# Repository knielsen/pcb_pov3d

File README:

PCB for 3D POV based on STM32F405 MCU and TLC5955 LED driver.

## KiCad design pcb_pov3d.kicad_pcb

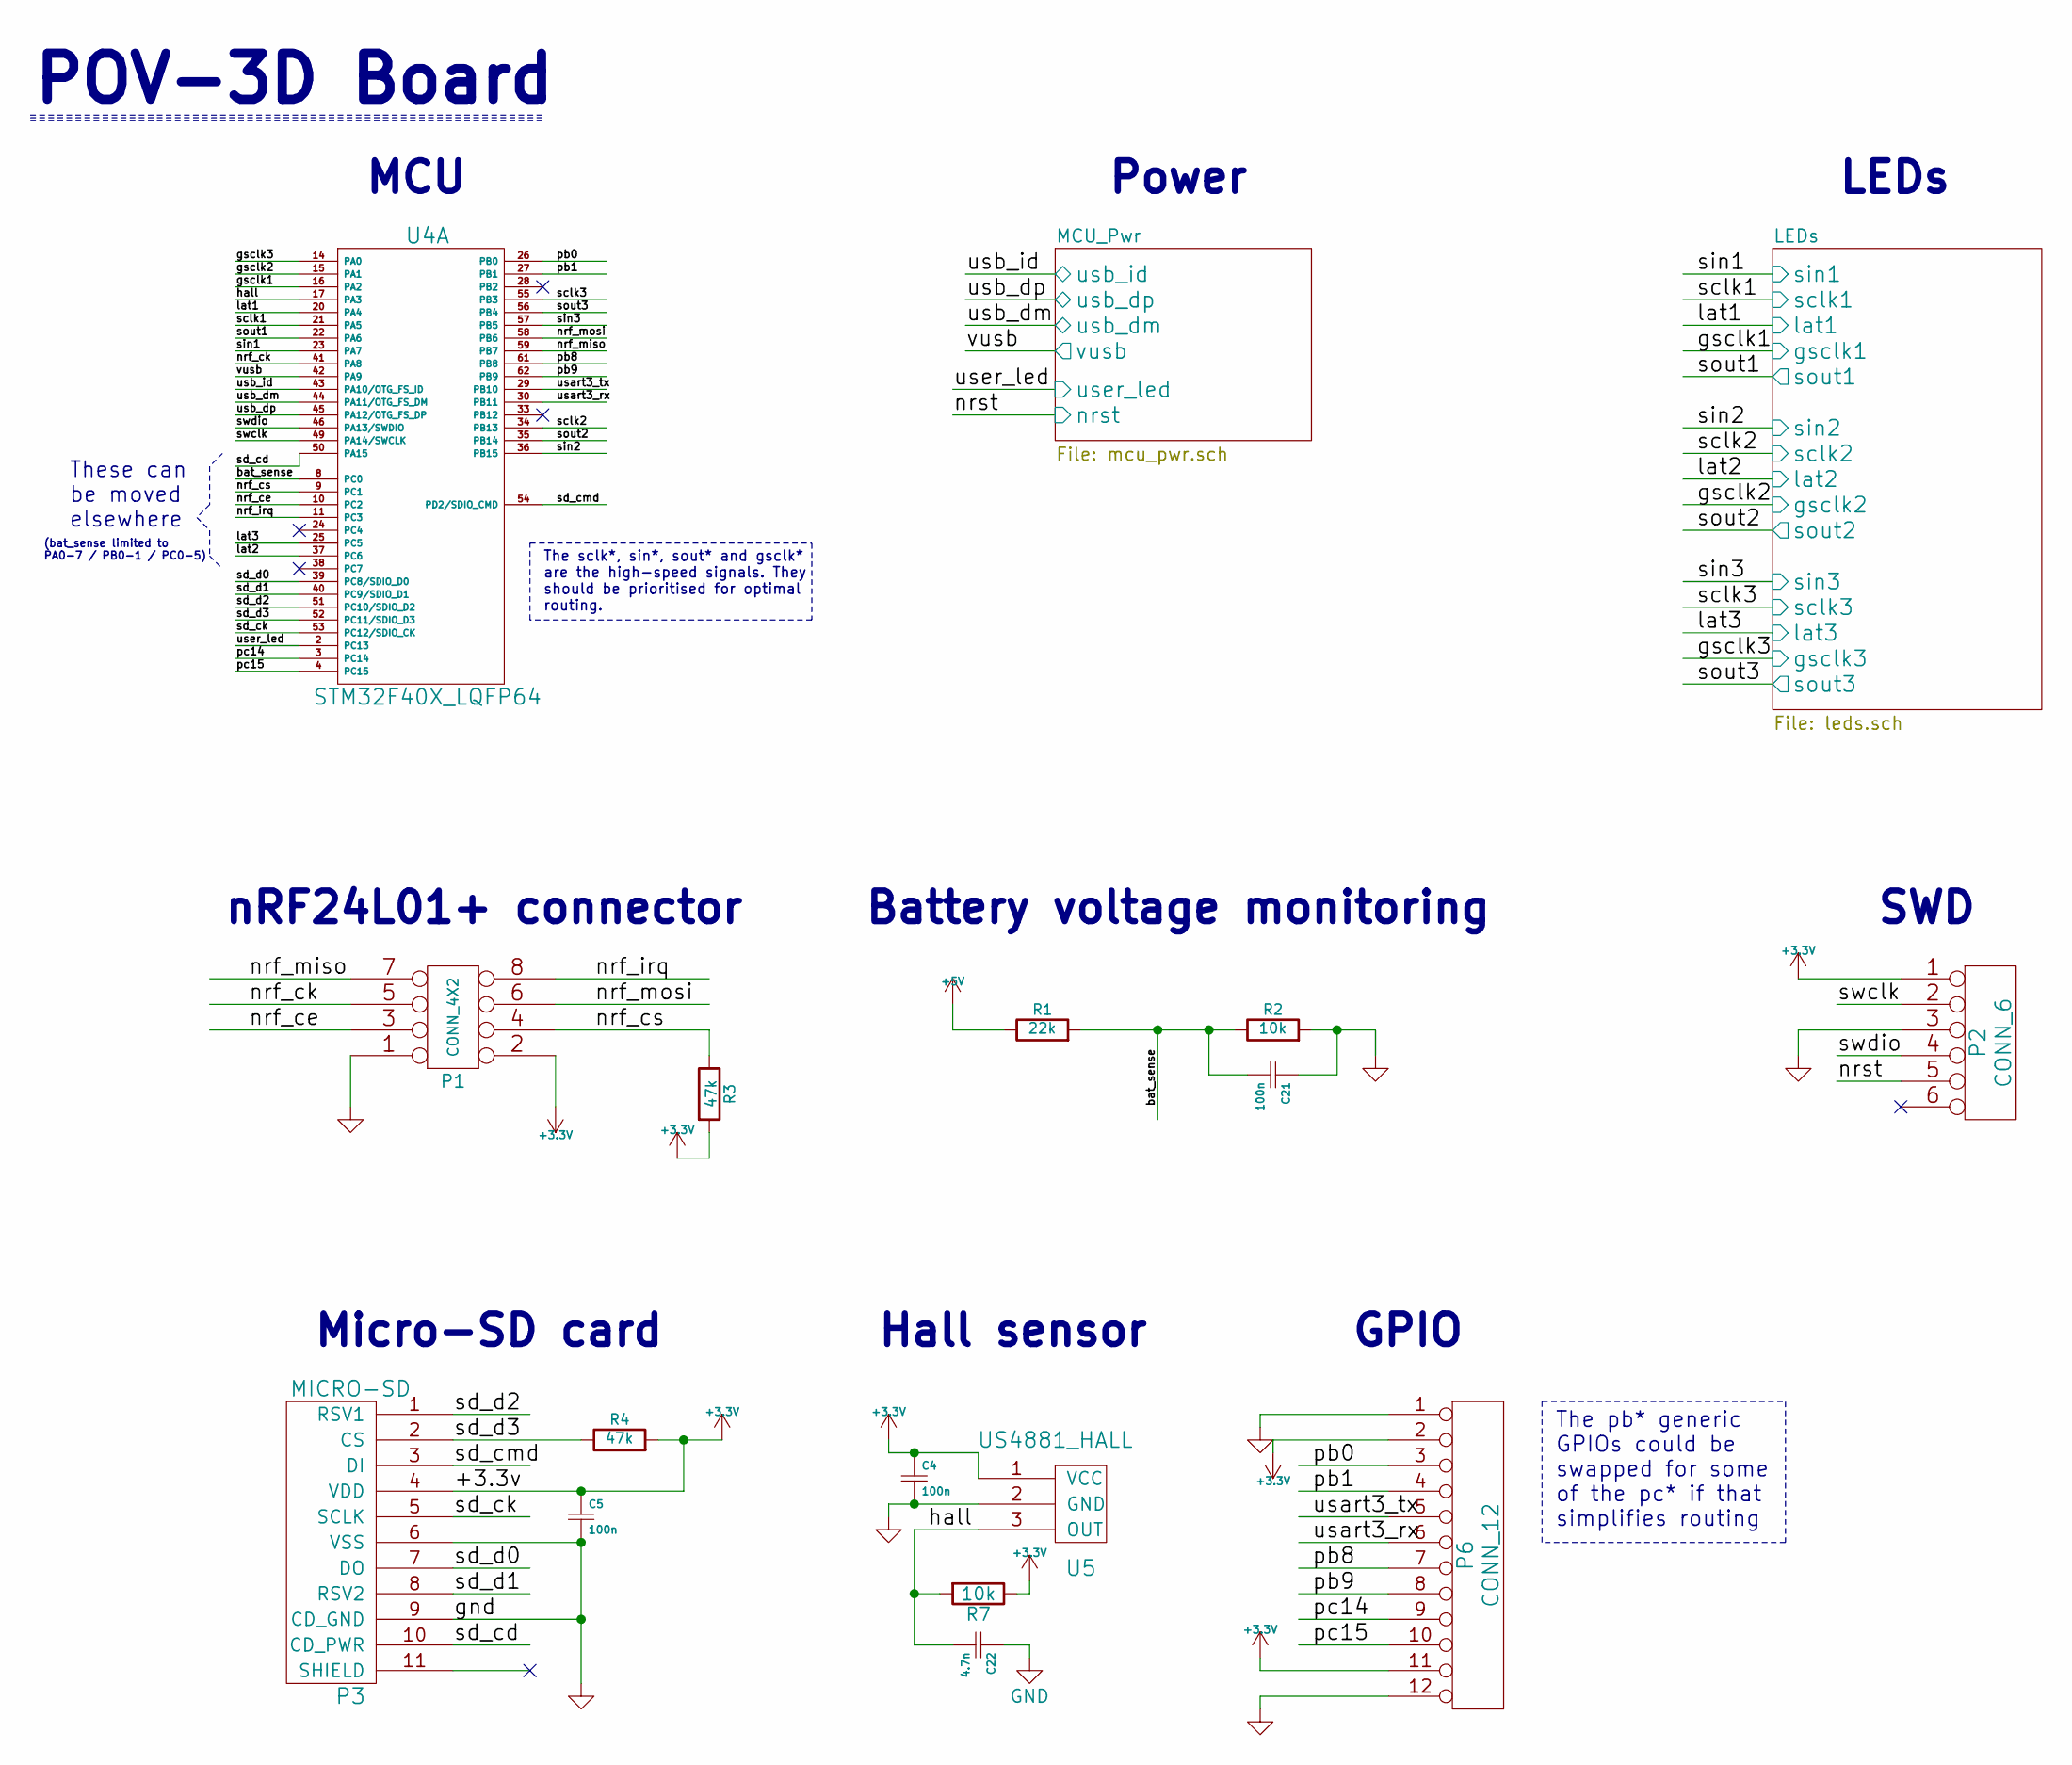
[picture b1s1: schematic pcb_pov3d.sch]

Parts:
C4, C5, C21: 100n; c_0805
C22: 4.7n; c_0805
P1: CONN_4X2; pin_socket_4x2
P2: CONN_6; pin_strip_6
P3: MICRO-SD; SD_502774
P6: CONN_12; pin_strip_12-90
R1: 22k; r_0805
R2, R7: 10k; r_0805
R3, R4: 47k; r_0805
U4: STM32F40X_LQFP64; LQFP_64
U5: US4881_HALL; TO92

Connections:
+3V3: C4.1, C5.1, P1.2, P2.1, P3.4 (VDD), P6.2, P6.11, R3.2, R4.2, R7.1, U5.1 (VCC); also elsewhere on the board
+5V: R1.1; also elsewhere on the board
/LEDs/gsclk1: U4.16 (PA2); also elsewhere on the board
/LEDs/gsclk2: U4.15 (PA1); also elsewhere on the board
/LEDs/gsclk3: U4.14 (PA0); also elsewhere on the board
/LEDs/lat1: U4.20 (PA4); also elsewhere on the board
/LEDs/lat2: U4.37 (PC6); also elsewhere on the board
/LEDs/lat3: U4.25 (PC5); also elsewhere on the board
/LEDs/sclk1: U4.21 (PA5); also elsewhere on the board
/LEDs/sclk2: U4.34 (PB13); also elsewhere on the board
/LEDs/sclk3: U4.55 (PB3); also elsewhere on the board
/LEDs/sin1: U4.23 (PA7); also elsewhere on the board
/LEDs/sin2: U4.36 (PB15); also elsewhere on the board
/LEDs/sin3: U4.57 (PB5); also elsewhere on the board
/LEDs/sout1: U4.22 (PA6); also elsewhere on the board
/LEDs/sout2: U4.35 (PB14); also elsewhere on the board
/LEDs/sout3: U4.56 (PB4); also elsewhere on the board
/MCU_Pwr/nrst: P2.5; also elsewhere on the board
/MCU_Pwr/usb_dm: U4.44 (PA11/OTG_FS_DM); also elsewhere on the board
/MCU_Pwr/usb_dp: U4.45 (PA12/OTG_FS_DP); also elsewhere on the board
/MCU_Pwr/usb_id: U4.43 (PA10/OTG_FS_ID); also elsewhere on the board
/MCU_Pwr/user_led: U4.2 (PC13); also elsewhere on the board
/MCU_Pwr/vusb: U4.42 (PA9); also elsewhere on the board
/bat_sense: C21.2, R1.2, R2.1, U4.8 (PC0)
/hall: C22.2, R7.2, U4.17 (PA3), U5.3 (OUT)
/nrf_ce: P1.3, U4.10 (PC2)
/nrf_ck: P1.5, U4.41 (PA8)
/nrf_cs: P1.4, R3.1, U4.9 (PC1)
/nrf_irq: P1.8, U4.11 (PC3)
/nrf_miso: P1.7, U4.59 (PB7)
/nrf_mosi: P1.6, U4.58 (PB6)
/pb0: P6.3, U4.26 (PB0)
/pb1: P6.4, U4.27 (PB1)
/pb8: P6.7, U4.61 (PB8)
/pb9: P6.8, U4.62 (PB9)
/pc14: P6.9, U4.3 (PC14)
/pc15: P6.10, U4.4 (PC15)
/sd_cd: P3.10 (CD_PWR), U4.50 (PA15)
/sd_ck: P3.5 (SCLK), U4.53 (PC12/SDIO_CK)
/sd_cmd: P3.3 (DI), U4.54 (PD2/SDIO_CMD)
/sd_d0: P3.7 (DO), U4.39 (PC8/SDIO_D0)
/sd_d1: P3.8 (RSV2), U4.40 (PC9/SDIO_D1)
/sd_d2: P3.1 (RSV1), U4.51 (PC10/SDIO_D2)
/sd_d3: P3.2 (CS), R4.1, U4.52 (PC11/SDIO_D3)
/swclk: P2.2, U4.49 (PA14/SWCLK)
/swdio: P2.4, U4.46 (PA13/SWDIO)
/usart3_rx: P6.6, U4.30 (PB11)
/usart3_tx: P6.5, U4.29 (PB10)
GND: C4.2, C5.2, C21.1, C22.1, P1.1, P2.3, P3.6 (VSS), P3.9 (CD_GND), P6.1, P6.12, R2.2, U5.2 (GND); also elsewhere on the board

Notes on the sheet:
nRF24L01+ connector
MCU
Micro-SD card
These can be moved elsewhere
(bat_sense limited to PA0-7 / PB0-1 / PC0-5)
Battery voltage monitoring
Power
LEDs
SWD
Hall sensor
GPIO
POV-3D Board
The sclk*, sin*, sout* and gsclk* are the high-speed signals. They should be prioritised for optimal routing.
The pb* generic GPIOs could be swapped for some of the pc* if that simplifies routing

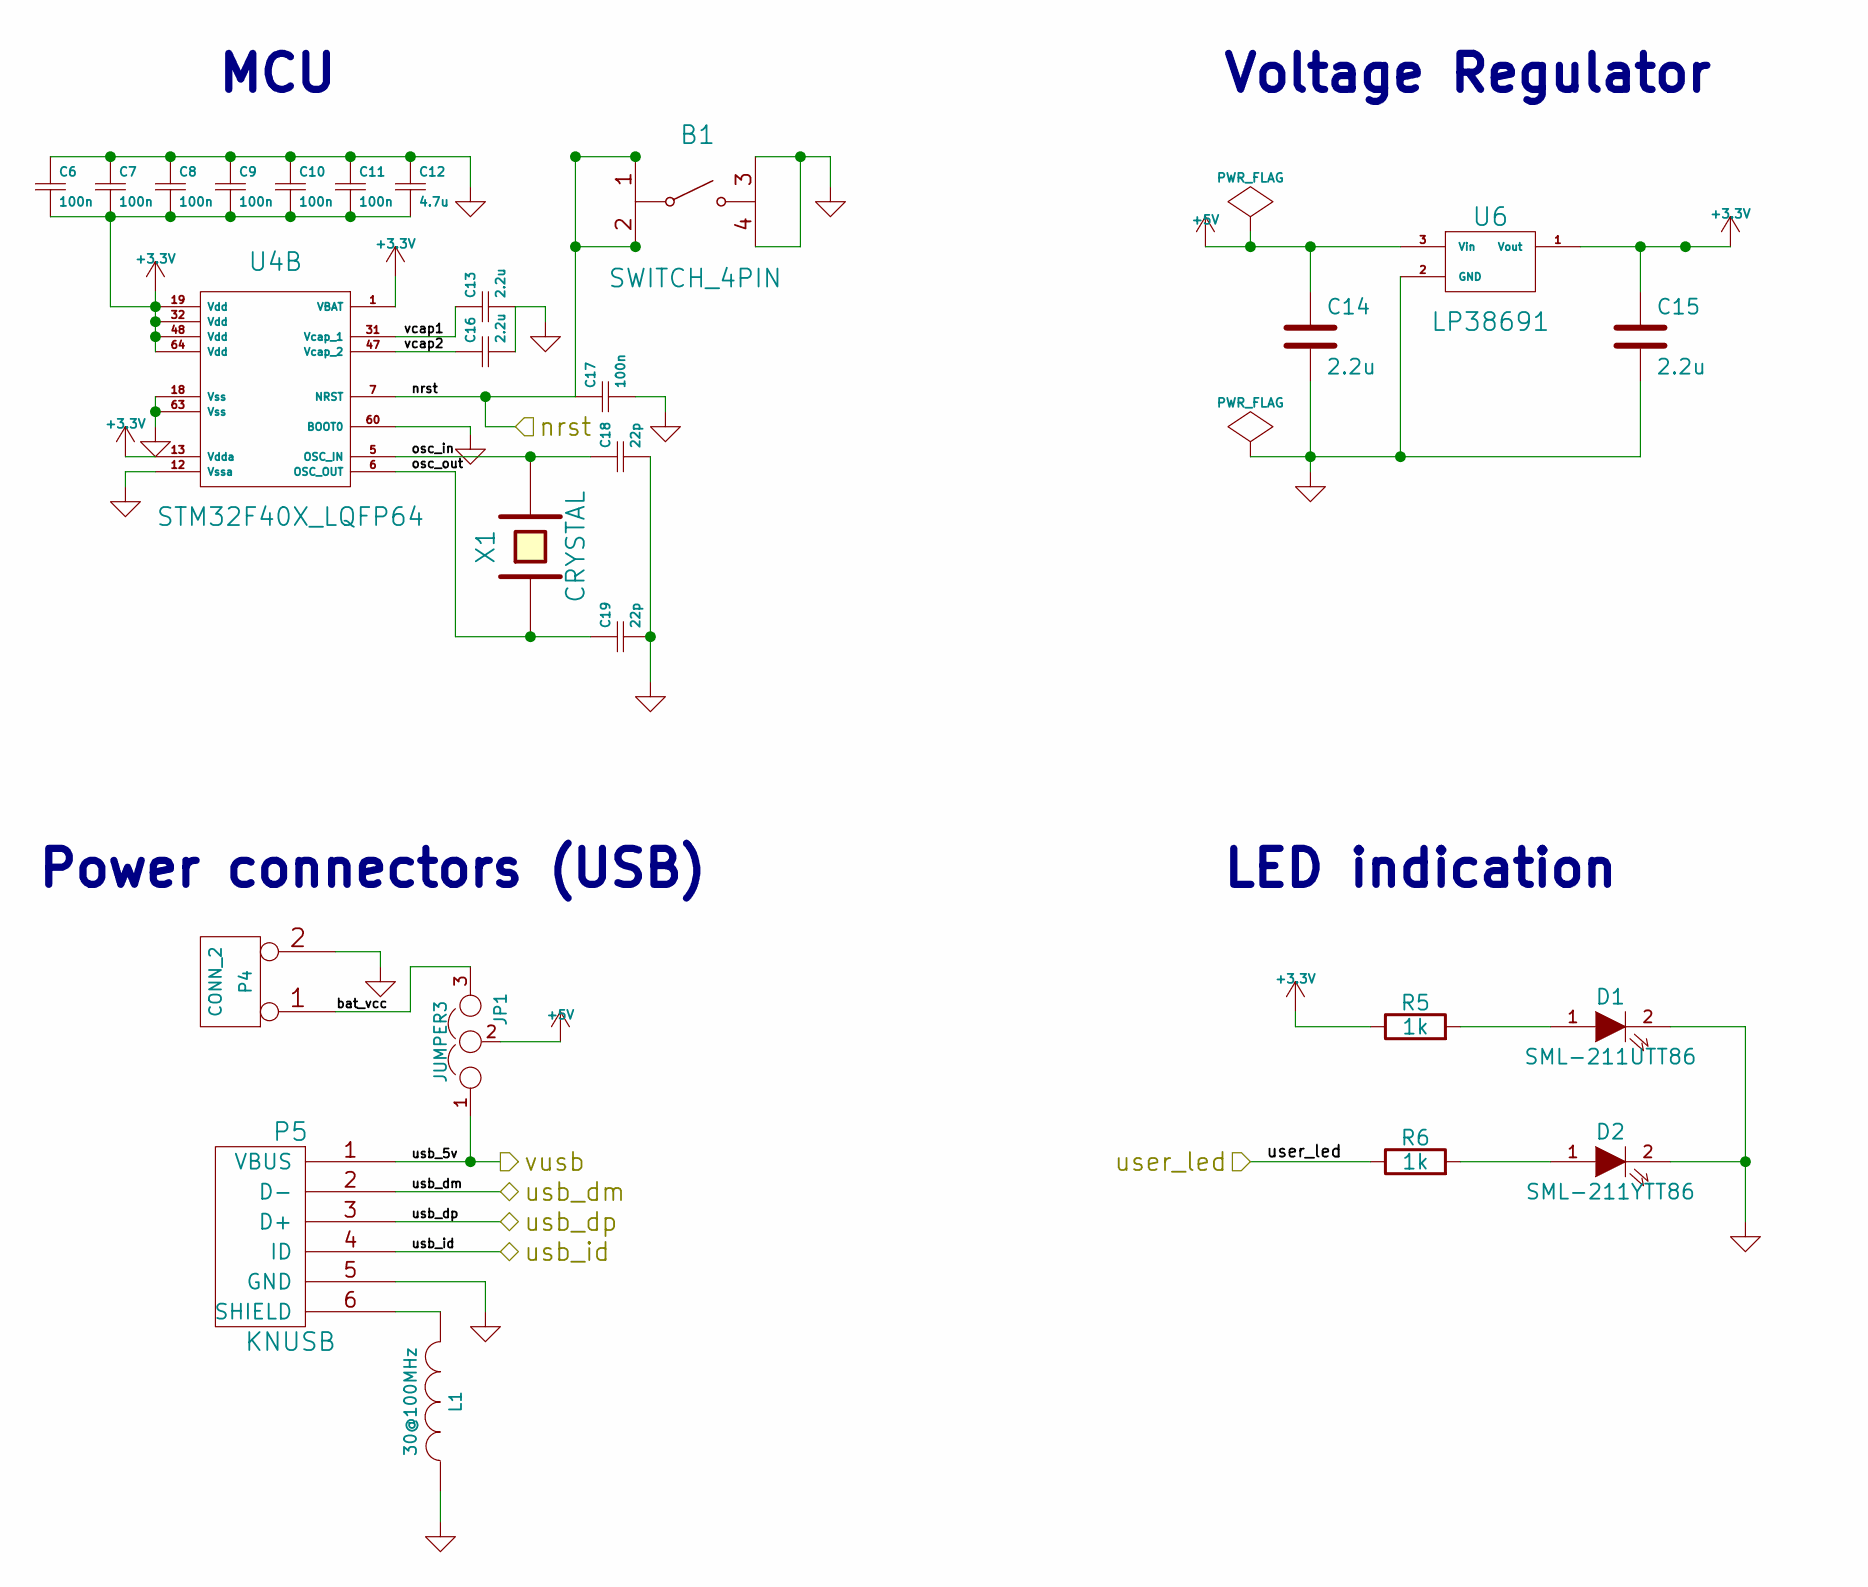
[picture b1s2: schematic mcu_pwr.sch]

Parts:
B1: SWITCH_4PIN; SWITCH_FSMJSMA
C6, C7, C8, C9, C10, C11, C17: 100n; c_0805
C12: 4.7u; c_0805
C13, C14, C15, C16: 2.2u; c_0805
C18, C19: 22p; c_0805
D1: SML-211UTT86; Led_0805
D2: SML-211YTT86; Led_0805
JP1: JUMPER3; pin_strip_3
L1: 30@100MHz; SMD-0603
P4: CONN_2; pin_strip_2-90
P5: KNUSB; 10103594-0001LF
R5, R6: 1k; r_0805
U4: STM32F40X_LQFP64; LQFP_64
U6: LP38691; TO-252-3
X1: CRYSTAL; 2-SOJ

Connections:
+3V3: C6.2, C7.2, C8.2, C9.2, C10.2, C11.2, C12.2, C15.1, R5.1, U4.1 (VBAT), U4.13 (Vdda), U4.19 (Vdd), U4.32 (Vdd), U4.48 (Vdd), U4.64 (Vdd), U6.1 (Vout); also elsewhere on the board
+5V: C14.1, JP1.2, U6.3 (Vin); also elsewhere on the board
/MCU_Pwr/bat_vcc: JP1.3, P4.1
/MCU_Pwr/nrst: B1.1, B1.2, C17.1, U4.7 (NRST); also elsewhere on the board
/MCU_Pwr/osc_in: C18.1, U4.5 (OSC_IN), X1.2
/MCU_Pwr/osc_out: C19.1, U4.6 (OSC_OUT), X1.1
/MCU_Pwr/usb_dm: P5.2 (D-); also elsewhere on the board
/MCU_Pwr/usb_dp: P5.3 (D+); also elsewhere on the board
/MCU_Pwr/usb_id: P5.4 (ID); also elsewhere on the board
/MCU_Pwr/user_led: R6.1; also elsewhere on the board
/MCU_Pwr/vcap1: C13.1, U4.31 (Vcap_1)
/MCU_Pwr/vcap2: C16.1, U4.47 (Vcap_2)
/MCU_Pwr/vusb: JP1.1, P5.1 (VBUS); also elsewhere on the board
GND: B1.3, B1.4, C6.1, C7.1, C8.1, C9.1, C10.1, C11.1, C12.1, C13.2, C14.2, C15.2, C16.2, C17.2, C18.2, C19.2, D1.2 (K), D2.2 (K), L1.1, P4.2 (PM), P5.5 (GND), U4.12 (Vssa), U4.18 (Vss), U4.60 (BOOT0), U4.63 (Vss), U6.2 (GND); also elsewhere on the board
unnamed: D1.1 (A), R5.2
unnamed: D2.1 (A), R6.2
unnamed: L1.2, P5.6 (SHIELD)

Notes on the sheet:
MCU
Voltage Regulator
Power connectors (USB)
LED indication

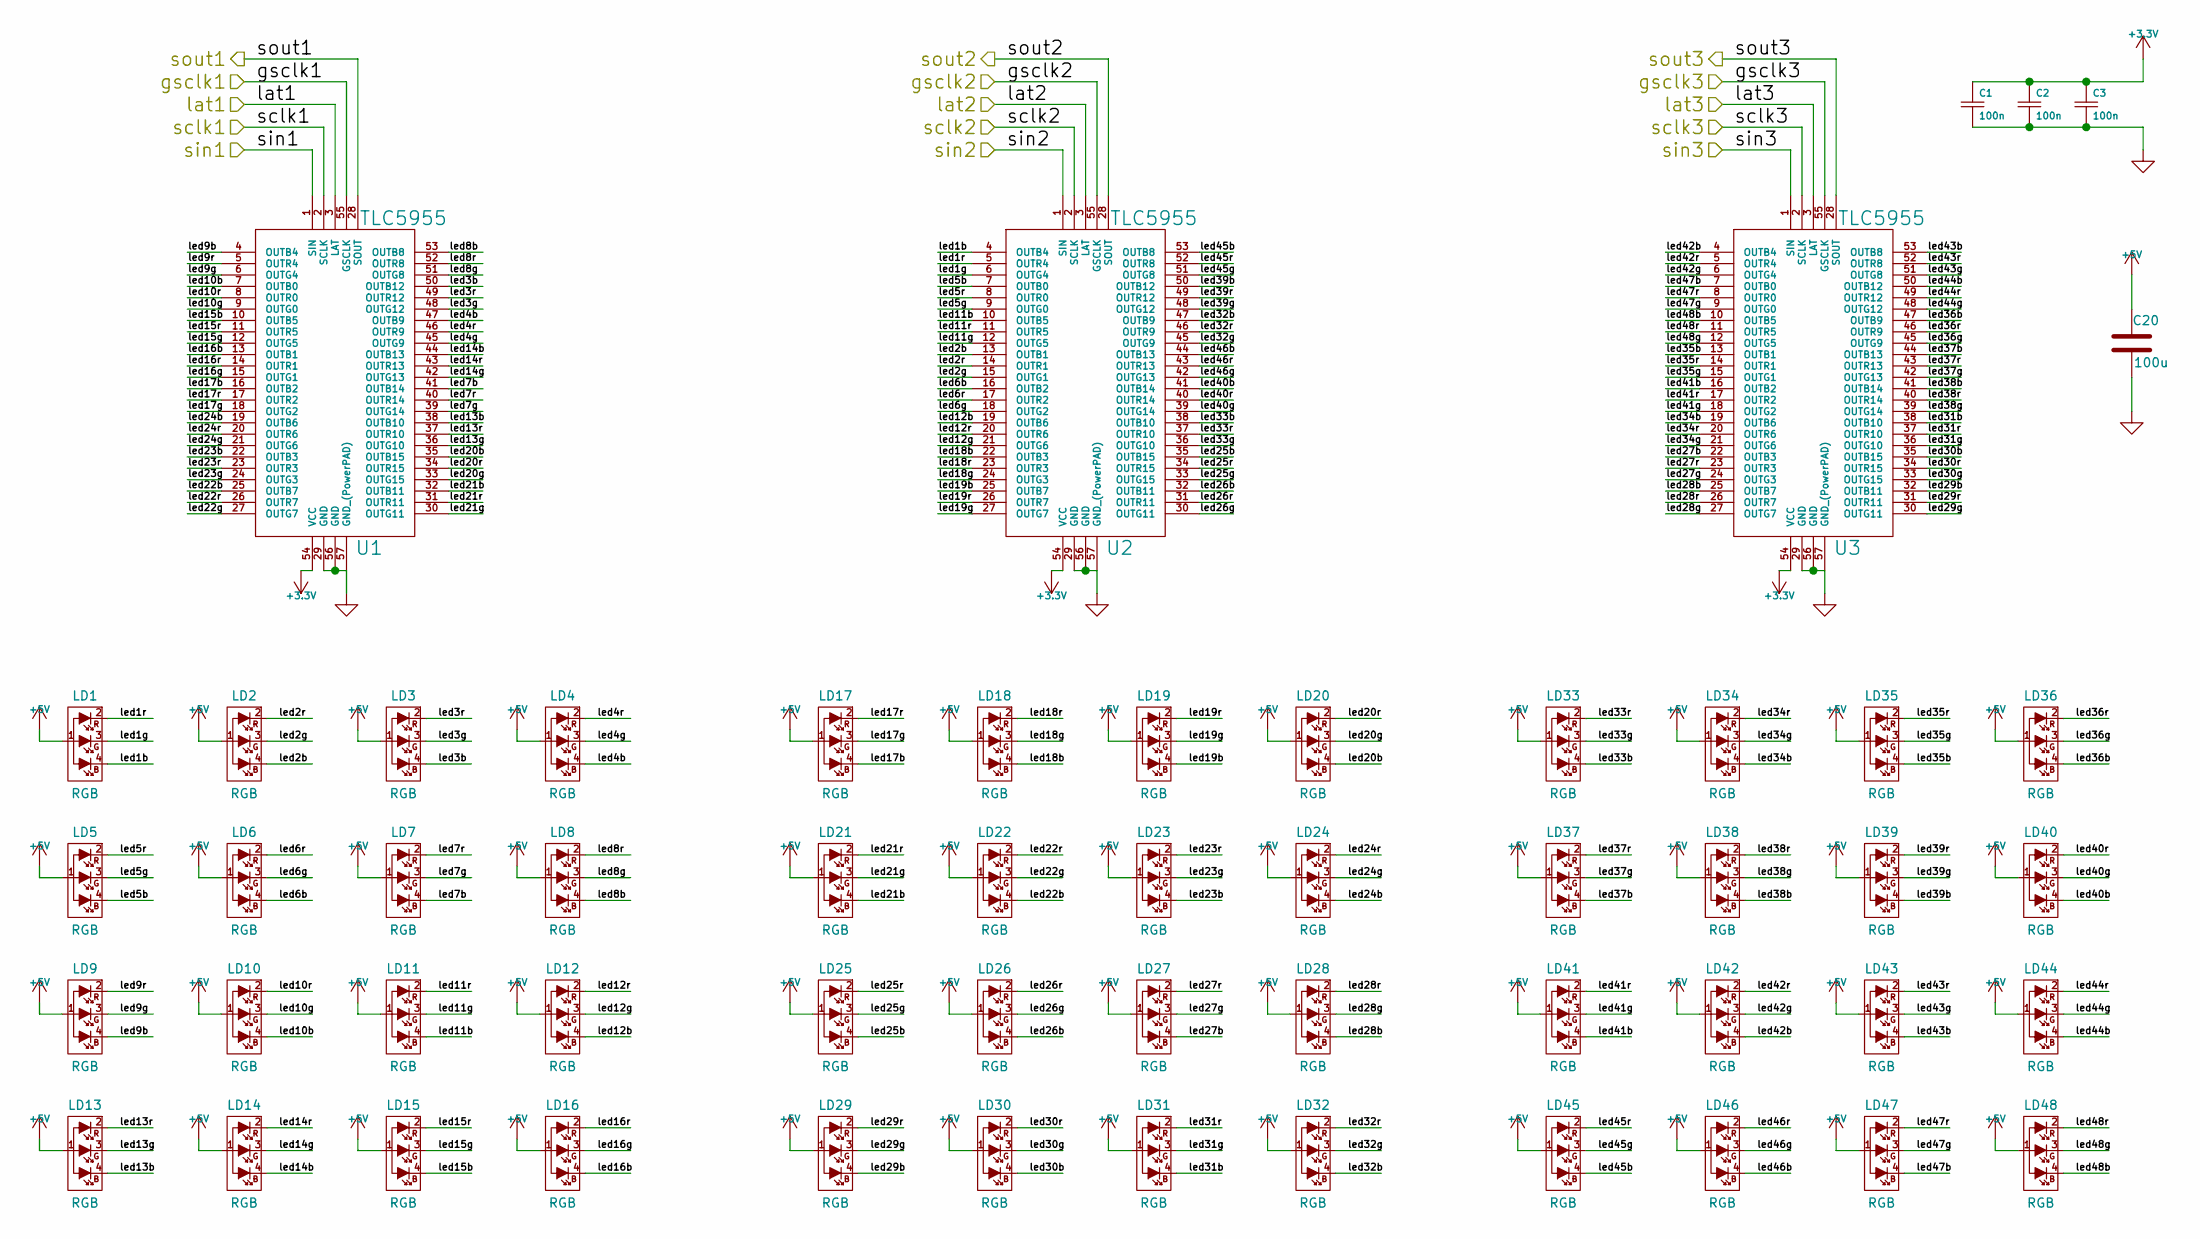
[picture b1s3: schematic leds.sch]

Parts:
C1, C2, C3: 100n; c_0805
C20: 100u; c_elec_6.3x5.8
LD1, LD2, LD3, LD4, LD5, LD6, LD7, LD8, LD9, LD10, LD11, LD12, LD13, LD14, LD15, LD16, LD17, LD18, LD19, LD20, LD21, LD22, LD23, LD24, LD25, LD26, LD27, LD28, LD29, LD30, LD31, LD32, LD33, LD34, LD35, LD36, LD37, LD38, LD39, LD40, LD41, LD42, LD43, LD44, LD45, LD46, LD47, LD48: RGB; RGB_0603
U1, U2, U3: TLC5955; TLC5955DCA

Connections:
+3V3: C1.1, C2.1, C3.1, U1.54 (VCC), U2.54 (VCC), U3.54 (VCC); also elsewhere on the board
+5V: C20.1, LD1.1 (AG), LD2.1 (AG), LD3.1 (AG), LD4.1 (AG), LD5.1 (AG), LD6.1 (AG), LD7.1 (AG), LD8.1 (AG), LD9.1 (AG), LD10.1 (AG), LD11.1 (AG), LD12.1 (AG), LD13.1 (AG), LD14.1 (AG), LD15.1 (AG), LD16.1 (AG), LD17.1 (AG), LD18.1 (AG), LD19.1 (AG), LD20.1 (AG), LD21.1 (AG), LD22.1 (AG), LD23.1 (AG), LD24.1 (AG), LD25.1 (AG), LD26.1 (AG), LD27.1 (AG), LD28.1 (AG), LD29.1 (AG), LD30.1 (AG), LD31.1 (AG), LD32.1 (AG), LD33.1 (AG), LD34.1 (AG), LD35.1 (AG), LD36.1 (AG), LD37.1 (AG), LD38.1 (AG), LD39.1 (AG), LD40.1 (AG), LD41.1 (AG), LD42.1 (AG), LD43.1 (AG), LD44.1 (AG), LD45.1 (AG), LD46.1 (AG), LD47.1 (AG), LD48.1 (AG); also elsewhere on the board
/LEDs/gsclk1: U1.55 (GSCLK); also elsewhere on the board
/LEDs/gsclk2: U2.55 (GSCLK); also elsewhere on the board
/LEDs/gsclk3: U3.55 (GSCLK); also elsewhere on the board
/LEDs/lat1: U1.3 (LAT); also elsewhere on the board
/LEDs/lat2: U2.3 (LAT); also elsewhere on the board
/LEDs/lat3: U3.3 (LAT); also elsewhere on the board
/LEDs/led1b: LD1.4 (CB), U2.4 (OUTB4)
/LEDs/led1g: LD1.3 (CG), U2.6 (OUTG4)
/LEDs/led1r: LD1.2 (CR), U2.5 (OUTR4)
/LEDs/led2b: LD2.4 (CB), U2.13 (OUTB1)
/LEDs/led2g: LD2.3 (CG), U2.15 (OUTG1)
/LEDs/led2r: LD2.2 (CR), U2.14 (OUTR1)
/LEDs/led3b: LD3.4 (CB), U1.50 (OUTB12)
/LEDs/led3g: LD3.3 (CG), U1.48 (OUTG12)
/LEDs/led3r: LD3.2 (CR), U1.49 (OUTR12)
/LEDs/led4b: LD4.4 (CB), U1.47 (OUTB9)
/LEDs/led4g: LD4.3 (CG), U1.45 (OUTG9)
/LEDs/led4r: LD4.2 (CR), U1.46 (OUTR9)
/LEDs/led5b: LD5.4 (CB), U2.7 (OUTB0)
/LEDs/led5g: LD5.3 (CG), U2.9 (OUTG0)
/LEDs/led5r: LD5.2 (CR), U2.8 (OUTR0)
/LEDs/led6b: LD6.4 (CB), U2.16 (OUTB2)
/LEDs/led6g: LD6.3 (CG), U2.18 (OUTG2)
/LEDs/led6r: LD6.2 (CR), U2.17 (OUTR2)
/LEDs/led7b: LD7.4 (CB), U1.41 (OUTB14)
/LEDs/led7g: LD7.3 (CG), U1.39 (OUTG14)
/LEDs/led7r: LD7.2 (CR), U1.40 (OUTR14)
/LEDs/led8b: LD8.4 (CB), U1.53 (OUTB8)
/LEDs/led8g: LD8.3 (CG), U1.51 (OUTG8)
/LEDs/led8r: LD8.2 (CR), U1.52 (OUTR8)
/LEDs/led9b: LD9.4 (CB), U1.4 (OUTB4)
/LEDs/led9g: LD9.3 (CG), U1.6 (OUTG4)
/LEDs/led9r: LD9.2 (CR), U1.5 (OUTR4)
/LEDs/led10b: LD10.4 (CB), U1.7 (OUTB0)
/LEDs/led10g: LD10.3 (CG), U1.9 (OUTG0)
/LEDs/led10r: LD10.2 (CR), U1.8 (OUTR0)
/LEDs/led11b: LD11.4 (CB), U2.10 (OUTB5)
/LEDs/led11g: LD11.3 (CG), U2.12 (OUTG5)
/LEDs/led11r: LD11.2 (CR), U2.11 (OUTR5)
/LEDs/led12b: LD12.4 (CB), U2.19 (OUTB6)
/LEDs/led12g: LD12.3 (CG), U2.21 (OUTG6)
/LEDs/led12r: LD12.2 (CR), U2.20 (OUTR6)
/LEDs/led13b: LD13.4 (CB), U1.38 (OUTB10)
/LEDs/led13g: LD13.3 (CG), U1.36 (OUTG10)
/LEDs/led13r: LD13.2 (CR), U1.37 (OUTR10)
/LEDs/led14b: LD14.4 (CB), U1.44 (OUTB13)
/LEDs/led14g: LD14.3 (CG), U1.42 (OUTG13)
/LEDs/led14r: LD14.2 (CR), U1.43 (OUTR13)
/LEDs/led15b: LD15.4 (CB), U1.10 (OUTB5)
/LEDs/led15g: LD15.3 (CG), U1.12 (OUTG5)
/LEDs/led15r: LD15.2 (CR), U1.11 (OUTR5)
/LEDs/led16b: LD16.4 (CB), U1.13 (OUTB1)
/LEDs/led16g: LD16.3 (CG), U1.15 (OUTG1)
/LEDs/led16r: LD16.2 (CR), U1.14 (OUTR1)
/LEDs/led17b: LD17.4 (CB), U1.16 (OUTB2)
/LEDs/led17g: LD17.3 (CG), U1.18 (OUTG2)
/LEDs/led17r: LD17.2 (CR), U1.17 (OUTR2)
/LEDs/led18b: LD18.4 (CB), U2.22 (OUTB3)
/LEDs/led18g: LD18.3 (CG), U2.24 (OUTG3)
/LEDs/led18r: LD18.2 (CR), U2.23 (OUTR3)
/LEDs/led19b: LD19.4 (CB), U2.25 (OUTB7)
/LEDs/led19g: LD19.3 (CG), U2.27 (OUTG7)
/LEDs/led19r: LD19.2 (CR), U2.26 (OUTR7)
/LEDs/led20b: LD20.4 (CB), U1.35 (OUTB15)
/LEDs/led20g: LD20.3 (CG), U1.33 (OUTG15)
/LEDs/led20r: LD20.2 (CR), U1.34 (OUTR15)
/LEDs/led21b: LD21.4 (CB), U1.32 (OUTB11)
/LEDs/led21g: LD21.3 (CG), U1.30 (OUTG11)
/LEDs/led21r: LD21.2 (CR), U1.31 (OUTR11)
/LEDs/led22b: LD22.4 (CB), U1.25 (OUTB7)
/LEDs/led22g: LD22.3 (CG), U1.27 (OUTG7)
/LEDs/led22r: LD22.2 (CR), U1.26 (OUTR7)
/LEDs/led23b: LD23.4 (CB), U1.22 (OUTB3)
/LEDs/led23g: LD23.3 (CG), U1.24 (OUTG3)
/LEDs/led23r: LD23.2 (CR), U1.23 (OUTR3)
/LEDs/led24b: LD24.4 (CB), U1.19 (OUTB6)
/LEDs/led24g: LD24.3 (CG), U1.21 (OUTG6)
/LEDs/led24r: LD24.2 (CR), U1.20 (OUTR6)
/LEDs/led25b: LD25.4 (CB), U2.35 (OUTB15)
/LEDs/led25g: LD25.3 (CG), U2.33 (OUTG15)
/LEDs/led25r: LD25.2 (CR), U2.34 (OUTR15)
/LEDs/led26b: LD26.4 (CB), U2.32 (OUTB11)
/LEDs/led26g: LD26.3 (CG), U2.30 (OUTG11)
/LEDs/led26r: LD26.2 (CR), U2.31 (OUTR11)
/LEDs/led27b: LD27.4 (CB), U3.22 (OUTB3)
/LEDs/led27g: LD27.3 (CG), U3.24 (OUTG3)
/LEDs/led27r: LD27.2 (CR), U3.23 (OUTR3)
/LEDs/led28b: LD28.4 (CB), U3.25 (OUTB7)
/LEDs/led28g: LD28.3 (CG), U3.27 (OUTG7)
/LEDs/led28r: LD28.2 (CR), U3.26 (OUTR7)
/LEDs/led29b: LD29.4 (CB), U3.32 (OUTB11)
/LEDs/led29g: LD29.3 (CG), U3.30 (OUTG11)
/LEDs/led29r: LD29.2 (CR), U3.31 (OUTR11)
/LEDs/led30b: LD30.4 (CB), U3.35 (OUTB15)
/LEDs/led30g: LD30.3 (CG), U3.33 (OUTG15)
/LEDs/led30r: LD30.2 (CR), U3.34 (OUTR15)
/LEDs/led31b: LD31.4 (CB), U3.38 (OUTB10)
/LEDs/led31g: LD31.3 (CG), U3.36 (OUTG10)
/LEDs/led31r: LD31.2 (CR), U3.37 (OUTR10)
/LEDs/led32b: LD32.4 (CB), U2.47 (OUTB9)
/LEDs/led32g: LD32.3 (CG), U2.45 (OUTG9)
/LEDs/led32r: LD32.2 (CR), U2.46 (OUTR9)
/LEDs/led33b: LD33.4 (CB), U2.38 (OUTB10)
/LEDs/led33g: LD33.3 (CG), U2.36 (OUTG10)
/LEDs/led33r: LD33.2 (CR), U2.37 (OUTR10)
/LEDs/led34b: LD34.4 (CB), U3.19 (OUTB6)
/LEDs/led34g: LD34.3 (CG), U3.21 (OUTG6)
/LEDs/led34r: LD34.2 (CR), U3.20 (OUTR6)
/LEDs/led35b: LD35.4 (CB), U3.13 (OUTB1)
/LEDs/led35g: LD35.3 (CG), U3.15 (OUTG1)
/LEDs/led35r: LD35.2 (CR), U3.14 (OUTR1)
/LEDs/led36b: LD36.4 (CB), U3.47 (OUTB9)
/LEDs/led36g: LD36.3 (CG), U3.45 (OUTG9)
/LEDs/led36r: LD36.2 (CR), U3.46 (OUTR9)
/LEDs/led37b: LD37.4 (CB), U3.44 (OUTB13)
/LEDs/led37g: LD37.3 (CG), U3.42 (OUTG13)
/LEDs/led37r: LD37.2 (CR), U3.43 (OUTR13)
/LEDs/led38b: LD38.4 (CB), U3.41 (OUTB14)
/LEDs/led38g: LD38.3 (CG), U3.39 (OUTG14)
/LEDs/led38r: LD38.2 (CR), U3.40 (OUTR14)
/LEDs/led39b: LD39.4 (CB), U2.50 (OUTB12)
/LEDs/led39g: LD39.3 (CG), U2.48 (OUTG12)
/LEDs/led39r: LD39.2 (CR), U2.49 (OUTR12)
/LEDs/led40b: LD40.4 (CB), U2.41 (OUTB14)
/LEDs/led40g: LD40.3 (CG), U2.39 (OUTG14)
/LEDs/led40r: LD40.2 (CR), U2.40 (OUTR14)
/LEDs/led41b: LD41.4 (CB), U3.16 (OUTB2)
/LEDs/led41g: LD41.3 (CG), U3.18 (OUTG2)
/LEDs/led41r: LD41.2 (CR), U3.17 (OUTR2)
/LEDs/led42b: LD42.4 (CB), U3.4 (OUTB4)
/LEDs/led42g: LD42.3 (CG), U3.6 (OUTG4)
/LEDs/led42r: LD42.2 (CR), U3.5 (OUTR4)
/LEDs/led43b: LD43.4 (CB), U3.53 (OUTB8)
/LEDs/led43g: LD43.3 (CG), U3.51 (OUTG8)
/LEDs/led43r: LD43.2 (CR), U3.52 (OUTR8)
/LEDs/led44b: LD44.4 (CB), U3.50 (OUTB12)
/LEDs/led44g: LD44.3 (CG), U3.48 (OUTG12)
/LEDs/led44r: LD44.2 (CR), U3.49 (OUTR12)
/LEDs/led45b: LD45.4 (CB), U2.53 (OUTB8)
/LEDs/led45g: LD45.3 (CG), U2.51 (OUTG8)
/LEDs/led45r: LD45.2 (CR), U2.52 (OUTR8)
/LEDs/led46b: LD46.4 (CB), U2.44 (OUTB13)
/LEDs/led46g: LD46.3 (CG), U2.42 (OUTG13)
/LEDs/led46r: LD46.2 (CR), U2.43 (OUTR13)
/LEDs/led47b: LD47.4 (CB), U3.7 (OUTB0)
/LEDs/led47g: LD47.3 (CG), U3.9 (OUTG0)
/LEDs/led47r: LD47.2 (CR), U3.8 (OUTR0)
/LEDs/led48b: LD48.4 (CB), U3.10 (OUTB5)
/LEDs/led48g: LD48.3 (CG), U3.12 (OUTG5)
/LEDs/led48r: LD48.2 (CR), U3.11 (OUTR5)
/LEDs/sclk1: U1.2 (SCLK); also elsewhere on the board
/LEDs/sclk2: U2.2 (SCLK); also elsewhere on the board
/LEDs/sclk3: U3.2 (SCLK); also elsewhere on the board
/LEDs/sin1: U1.1 (SIN); also elsewhere on the board
/LEDs/sin2: U2.1 (SIN); also elsewhere on the board
/LEDs/sin3: U3.1 (SIN); also elsewhere on the board
/LEDs/sout1: U1.28 (SOUT); also elsewhere on the board
/LEDs/sout2: U2.28 (SOUT); also elsewhere on the board
/LEDs/sout3: U3.28 (SOUT); also elsewhere on the board
GND: C1.2, C2.2, C3.2, C20.2, U1.29 (GND), U1.56 (GND), U1.57 (GND_(PowerPAD)), U2.29 (GND), U2.56 (GND), U2.57 (GND_(PowerPAD)), U3.29 (GND), U3.56 (GND), U3.57 (GND_(PowerPAD)); also elsewhere on the board

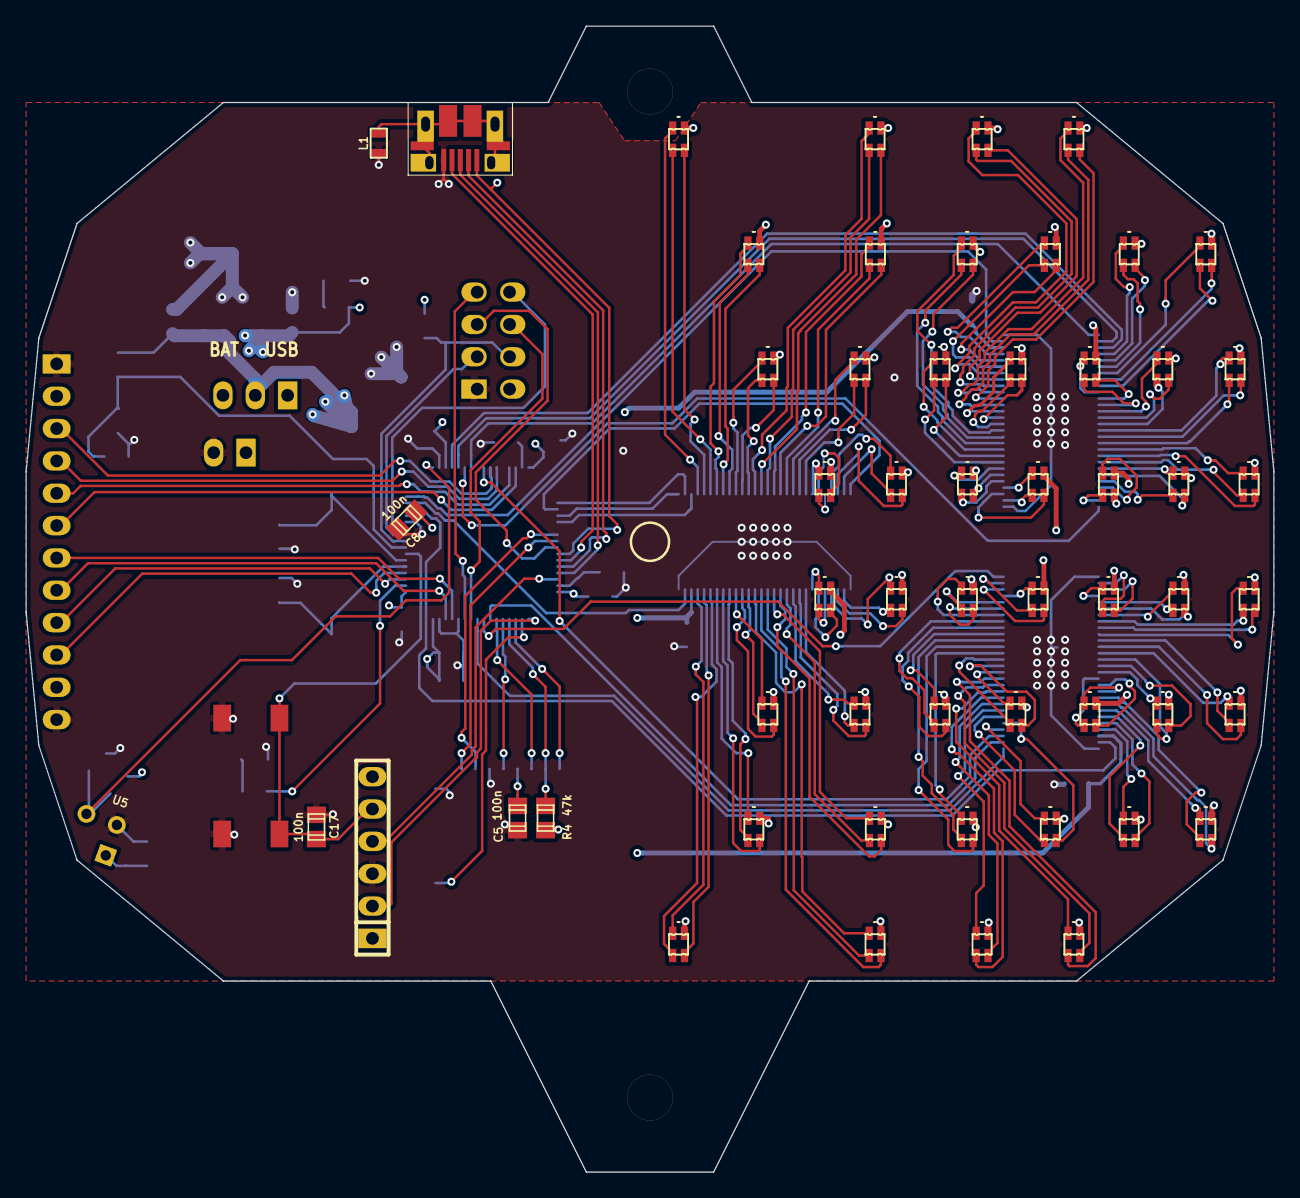
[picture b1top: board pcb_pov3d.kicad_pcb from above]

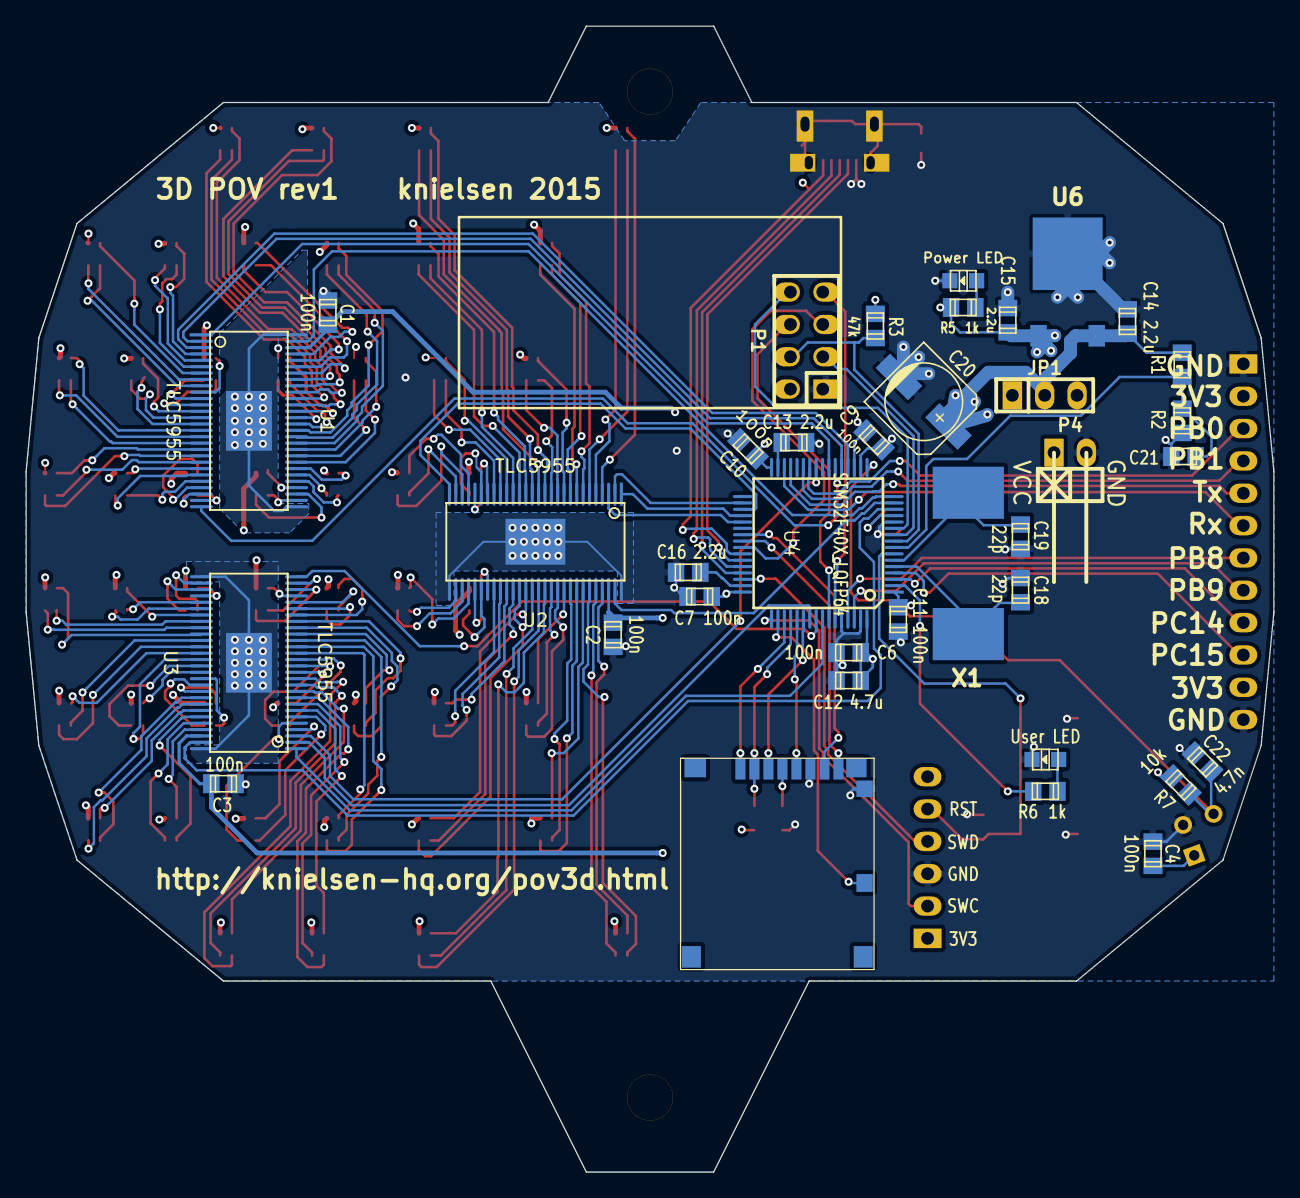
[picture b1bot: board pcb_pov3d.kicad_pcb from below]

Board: 4 copper layers, 98.0 x 90.0 mm, 95 parts (37 on the bottom side), 201 nets.

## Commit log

2015-01-10 Add tlc5955 powerpad to schematics
2015-01-11 Misc. tweaks. Schematics is getting closer now.
2015-01-18 Tweaks.
2015-01-28 Updated for new KiCAD version (though still a few glitches in the schematics)
2015-01-28 Fix CSMALL <-> Csmall glitch when converting to new version
2015-01-28 Fix offset on multi-line texts after import to new KiCAD version.
2015-01-28 Place RGB LEDs in the computed pattern for 3D POV effect.
2015-01-29 Assignment of LEDs to TLC5955 outputs.
2015-01-29 Powerpads on TLC5955's, and sketch of high-speed signals routing.
2015-01-30 LED routing, and initial placement of most remaining components.
2015-01-30 Routing
2015-02-03 Most signals routed (still some power/gnd to route)
2015-02-03 Complete routing
2015-02-03 Routing tweaks.
2015-02-16 Misc. changes.
2015-04-15 fix one 3d shape for new kicad
2015-04-15 Fix remaining 3d-shapes for new kicad.
2015-04-27 Fixup some missing wires after kicad upgrade
    (A resistor and a capacitor component now has shorter leads, it seems.
2015-04-29 Mounting holes - need some work, too close to LED.
2015-04-30 Improved mounting holes.
2015-05-01 Move 2 TLCs 4mm to not conflict with spindle mount rim
2015-05-02 Misc. cleanup of the routing.
2015-05-02 Move power connector and jumper away from rim of spindle_mount
2015-05-02 Move programmer connector away from rim of spindle_mount
2015-05-02 Clean up mounting hole silkscreens.
2015-05-02 Silkscreen tweaks.
2015-05-03 More silkscreen tweaks.
2015-05-03 More silk screen. Should be fairly close now.
2015-05-03 One more silk screen update
2015-05-03 Add pull-up and capacitor on Hall output
2015-05-03 Misc. minor tweaks
2015-05-03 Tweaks
2015-05-06 Final rev1 gerbers ordered from SeeedStudio.
